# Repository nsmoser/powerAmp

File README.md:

Audio amplifier project implementing the LM3886 audio power amplifier.
Originally intended to replace a busted board in a powered subwoofer, but designed to be reused as a L/R stereo amp.
NOTE: the mute circuit was incorrectly connected to ground instead of the negative rail. Current draw necessary to unmute cannot be achieved unless the switch is connected to the negative rail.
Realistically, not all three matching pairs of caps in the cap bank are necessary. Connect the mute switch to one of the negative rail through holes in the cap bank if the bank isn't fully populated.
The low voltage power components are also not necessary for function. They are there to power peripherals (indicator lights, add-on pre-filters or pre-amps, etc.)

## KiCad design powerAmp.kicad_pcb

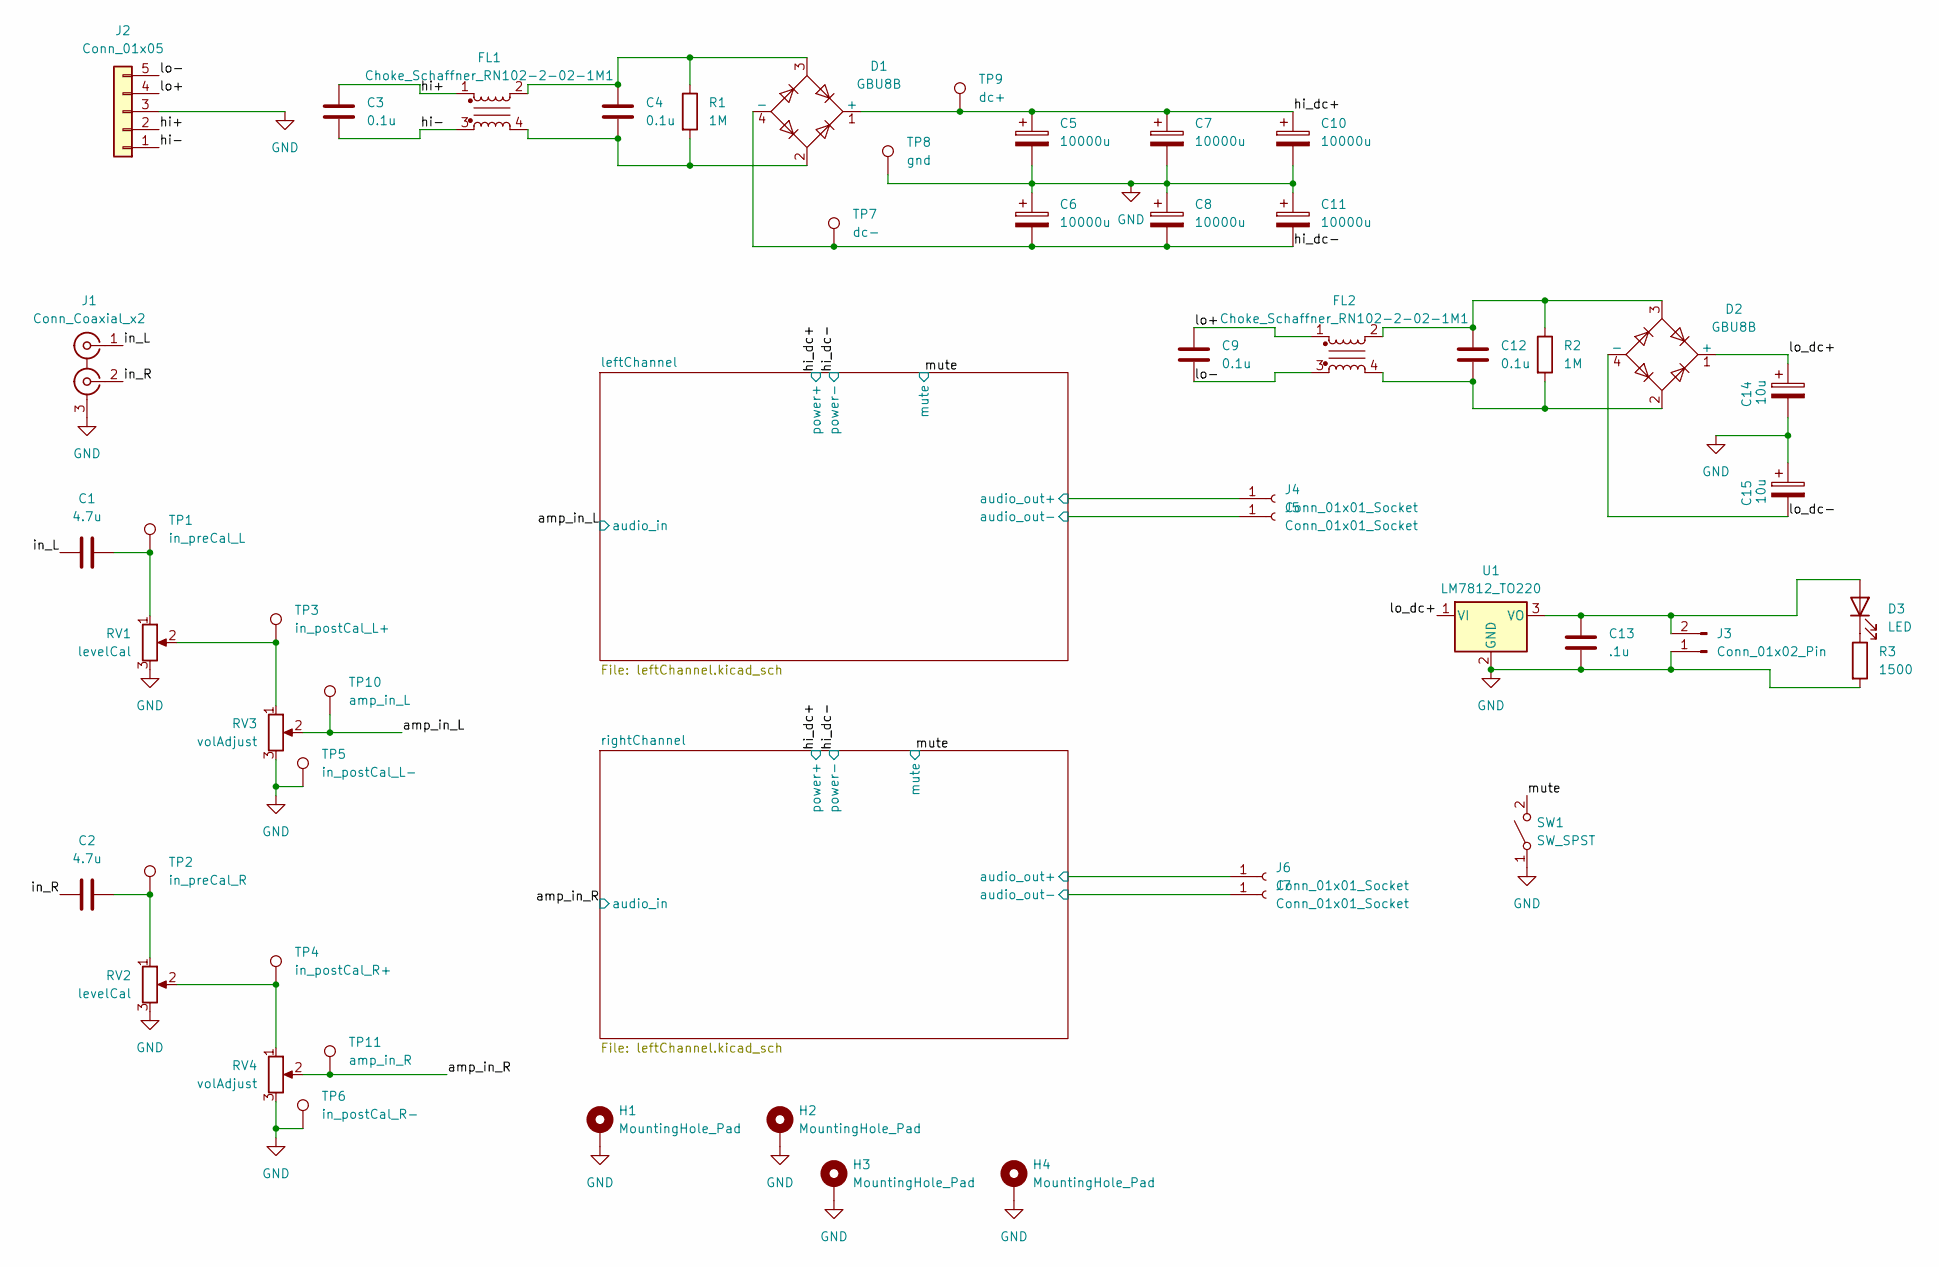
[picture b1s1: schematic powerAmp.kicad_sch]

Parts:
C1, C2: 4.7u; C_0805_2012Metric
C3, C4, C9, C12: 0.1u; C_1206_3216Metric
C5, C6, C7, C8, C10, C11: 10000u; CP_Radial_D35.0mm_P10.00mm_SnapIn
C13: .1u; C_0402_1005Metric
C14, C15: 10u; CP_Elec_5x5.3
D1, D2: GBU8B; Diode_Bridge_Vishay_GBU
D3: LED; PinSocket_1x02_P2.54mm_Vertical
FL1, FL2: Choke_Schaffner_RN102-2-02-1M1; Choke_Schaffner_RN102-04-14.0x14.0mm
H1, H2, H3, H4: MountingHole_Pad; MountingHole_4.3mm_M4_Pad_TopBottom
J1: Conn_Coaxial_x2; PinSocket_1x03_P2.54mm_Vertical
J2: Conn_01x05; PinSocket_1x05_P2.54mm_Vertical
J3: Conn_01x02_Pin; PinSocket_1x02_P2.54mm_Vertical
J4, J5, J6, J7: Conn_01x01_Socket; PinSocket_1x01_P2.54mm_Vertical
R1, R2: 1M; R_2512_6332Metric
R3: 1500; R_0603_1608Metric
RV1, RV2: levelCal; Potentiometer_Bourns_3009P_Horizontal
RV3, RV4: volAdjust; PinSocket_1x03_P2.54mm_Vertical
SW1: SW_SPST; PinSocket_1x02_P2.54mm_Vertical
TP1: in_preCal_L; TestPoint_Pad_1.0x1.0mm
TP2: in_preCal_R; TestPoint_Pad_1.0x1.0mm
TP3: in_postCal_L+; PinHeader_1x01_P2.54mm_Vertical
TP4: in_postCal_R+; PinHeader_1x01_P2.54mm_Vertical
TP5: in_postCal_L-; PinHeader_1x01_P2.54mm_Vertical
TP6: in_postCal_R-; PinHeader_1x01_P2.54mm_Vertical
TP7: dc-; TestPoint_Pad_1.0x1.0mm
TP8: gnd; TestPoint_Pad_1.0x1.0mm
TP9: dc+; TestPoint_Pad_1.0x1.0mm
TP10: amp_in_L; PinHeader_1x01_P2.54mm_Vertical
TP11: amp_in_R; PinHeader_1x01_P2.54mm_Vertical
U1: LM7812_TO220; TO-220-3_Vertical

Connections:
/amp_in_L: RV3.2, TP10.1; also elsewhere on the board
/amp_in_R: RV4.2, TP11.1; also elsewhere on the board
/hi+: C3.1, FL1.1, J2.2
/hi-: C3.2, FL1.3, J2.1
/hi_dc+: C5.1, C7.1, C10.1, D1.1 (+), TP9.1; also elsewhere on the board
/hi_dc-: C6.2, C8.2, C11.2, D1.4 (-), TP7.1; also elsewhere on the board
/in_L: C1.1, J1.1 (IN1)
/in_R: C2.1, J1.2 (IN2)
/leftChannel/audio_out+: J4.1; also elsewhere on the board
/leftChannel/audio_out-: J5.1; also elsewhere on the board
/lo+: C9.1, FL2.1, J2.4
/lo-: C9.2, FL2.3, J2.5
/lo_dc+: C14.1, D2.1 (+), U1.1 (VI)
/lo_dc-: C15.2, D2.4 (-)
/mute: SW1.2 (B); also elsewhere on the board
/rightChannel/audio_out+: J6.1; also elsewhere on the board
/rightChannel/audio_out-: J7.1; also elsewhere on the board
GND: C5.2, C6.1, C7.2, C8.1, C10.2, C11.1, C13.1, C14.2, C15.1, H1.1, H2.1, H3.1, H4.1, J1.3 (EXT), J2.3, J3.1, R3.2, RV1.3, RV2.3, RV3.3, RV4.3, SW1.1 (A), TP5.1, TP6.1, TP8.1, U1.2 (GND); also elsewhere on the board
unnamed: C1.2, RV1.1, TP1.1
unnamed: C2.2, RV2.1, TP2.1
unnamed: C4.1, D1.3, FL1.2, R1.1
unnamed: C4.2, D1.2, FL1.4, R1.2
unnamed: C12.1, D2.3, FL2.2, R2.1
unnamed: C12.2, D2.2, FL2.4, R2.2
unnamed: C13.2, D3.2 (A), J3.2, U1.3 (VO)
unnamed: D3.1 (K), R3.1
unnamed: RV1.2, RV3.1, TP3.1
unnamed: RV2.2, RV4.1, TP4.1

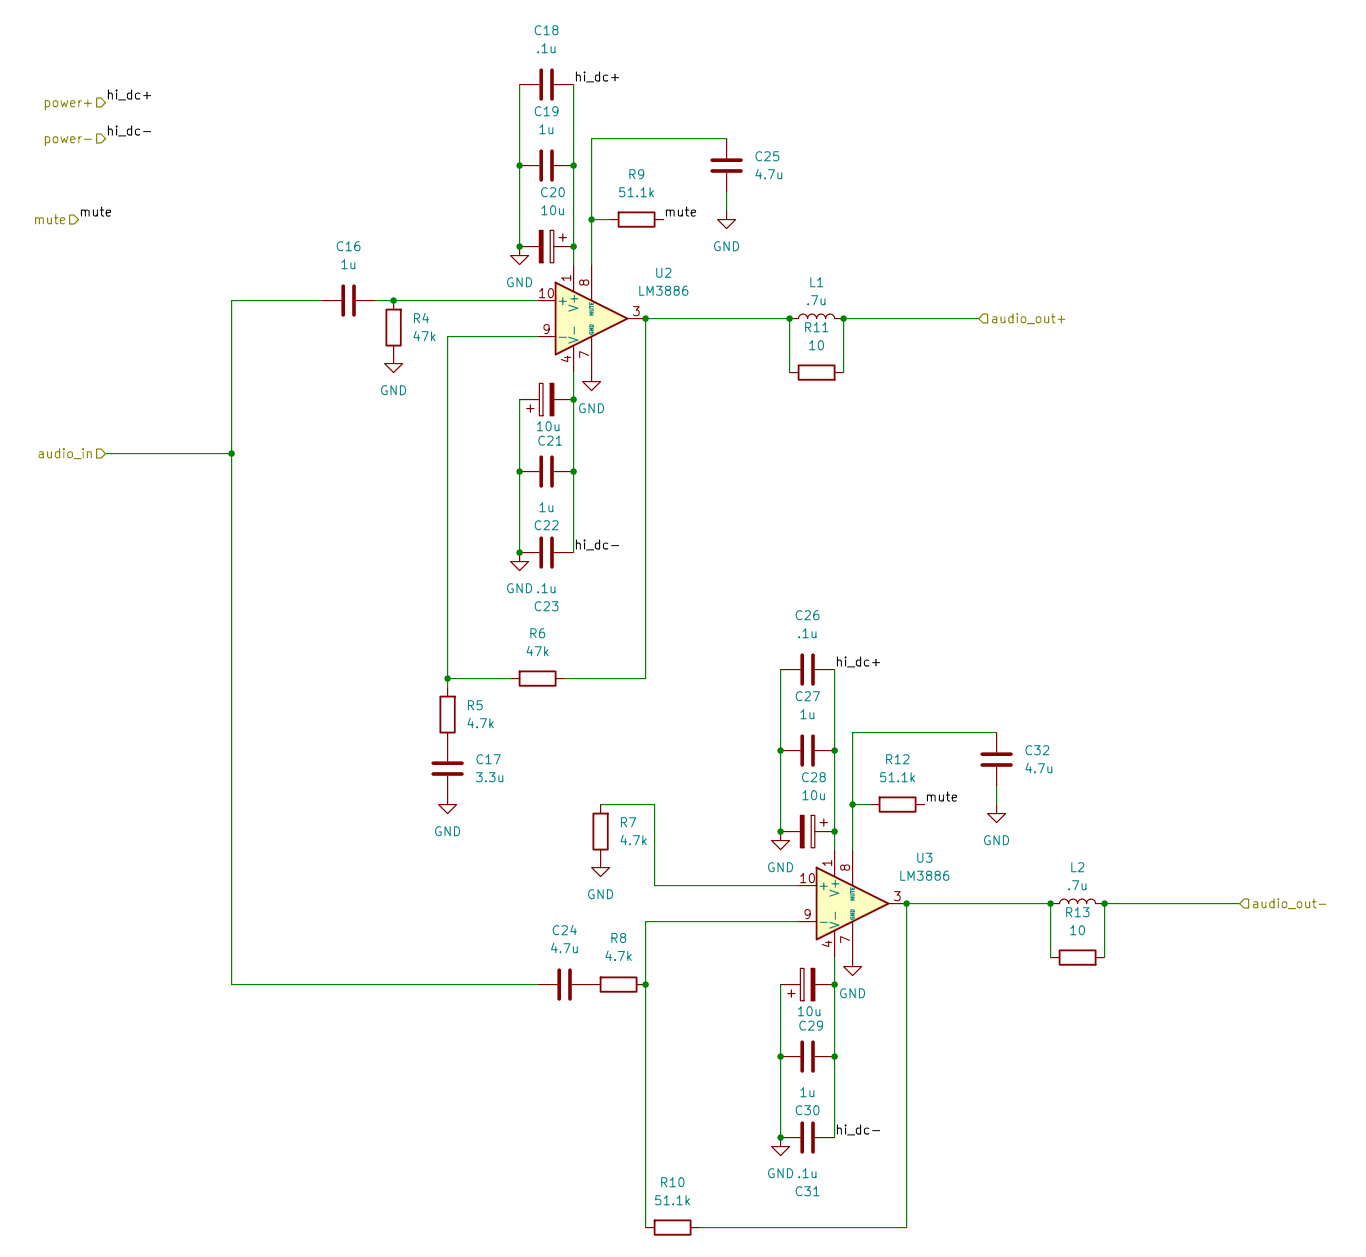
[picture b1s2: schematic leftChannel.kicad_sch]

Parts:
C16, C19, C22, C27, C30: 1u; C_0805_2012Metric
C17: 3.3u; C_1210_3225Metric
C18, C23, C26, C31: .1u; C_0402_1005Metric
C20, C21, C28, C29: 10u; CP_Elec_5x5.3
C24, C25, C32: 4.7u; C_0805_2012Metric
L1, L2: .7u; L_Vishay_IHLP-1616
R4, R6: 47k; R_0603_1608Metric
R5, R7, R8: 4.7k; R_0603_1608Metric
R9, R10, R12: 51.1k; R_0603_1608Metric
R11, R13: 10; PinSocket_1x02_P2.54mm_Vertical
U2, U3: LM3886; TO-220F-11_P3.4x5.08mm_StaggerOdd_Lead5.08mm_Vertical

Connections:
/amp_in_L: C16.1, C24.1; also elsewhere on the board
/hi_dc+: C18.2, C19.2, C20.1, C26.2, C27.2, C28.1, U2.1 (V+), U2.5 (V+), U3.1 (V+), U3.5 (V+); also elsewhere on the board
/hi_dc-: C21.2, C22.1, C23.1, C29.2, C30.1, C31.1, U2.4 (V-), U3.4 (V-); also elsewhere on the board
/leftChannel/audio_out+: L1.2, R11.2; also elsewhere on the board
/leftChannel/audio_out-: L2.2, R13.2; also elsewhere on the board
/mute: R9.1, R12.1; also elsewhere on the board
GND: C17.1, C18.1, C19.1, C20.2, C21.1, C22.2, C23.2, C25.1, C26.1, C27.1, C28.2, C29.1, C30.2, C31.2, C32.1, R4.1, R7.1, U2.7 (GND), U3.7 (GND); also elsewhere on the board
unnamed: C17.2, R5.1
unnamed: C24.2, R8.2
unnamed: L1.1, R6.1, R11.1, U2.3
unnamed: L2.1, R10.1, R13.1, U3.3
unnamed: C16.2, R4.2, U2.10 (+)
unnamed: R5.2, R6.2, U2.9 (-)
unnamed: C25.2, R9.2, U2.8 (MUTE)
unnamed: R7.2, U3.10 (+)
unnamed: R8.1, R10.2, U3.9 (-)
unnamed: C32.2, R12.2, U3.8 (MUTE)

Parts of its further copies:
C33, C36, C39, C44, C47: 1u; C_0805_2012Metric
C34: 3.3u; C_1210_3225Metric
C35, C40, C43, C48: .1u; C_0402_1005Metric
C37, C38, C45, C46: 10u; CP_Elec_5x5.3
C41, C42, C49: 4.7u; C_0805_2012Metric
L3, L4: .7u; L_Vishay_IHLP-1616
R14, R16: 47k; R_0603_1608Metric
R15, R17, R18: 4.7k; R_0603_1608Metric
R19, R20, R22: 51.1k; R_0603_1608Metric
R21, R23: 10; PinSocket_1x02_P2.54mm_Vertical
U4, U5: LM3886; TO-220F-11_P3.4x5.08mm_StaggerOdd_Lead5.08mm_Vertical

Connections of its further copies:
/amp_in_R: C33.1, C41.1; also elsewhere on the board
/hi_dc+: C35.2, C36.2, C37.1, C43.2, C44.2, C45.1, U4.1 (V+), U4.5 (V+), U5.1 (V+), U5.5 (V+); also elsewhere on the board
/hi_dc-: C38.2, C39.1, C40.1, C46.2, C47.1, C48.1, U4.4 (V-), U5.4 (V-); also elsewhere on the board
/mute: R19.1, R22.1; also elsewhere on the board
/rightChannel/audio_out+: L3.2, R21.2; also elsewhere on the board
/rightChannel/audio_out-: L4.2, R23.2; also elsewhere on the board
GND: C34.1, C35.1, C36.1, C37.2, C38.1, C39.2, C40.2, C42.1, C43.1, C44.1, C45.2, C46.1, C47.2, C48.2, C49.1, R14.1, R17.1, U4.7 (GND), U5.7 (GND); also elsewhere on the board
unnamed: C34.2, R15.1
unnamed: C41.2, R18.2
unnamed: L3.1, R16.1, R21.1, U4.3
unnamed: L4.1, R20.1, R23.1, U5.3
unnamed: C33.2, R14.2, U4.10 (+)
unnamed: R15.2, R16.2, U4.9 (-)
unnamed: C42.2, R19.2, U4.8 (MUTE)
unnamed: R17.2, U5.10 (+)
unnamed: R18.1, R20.2, U5.9 (-)
unnamed: C49.2, R22.2, U5.8 (MUTE)

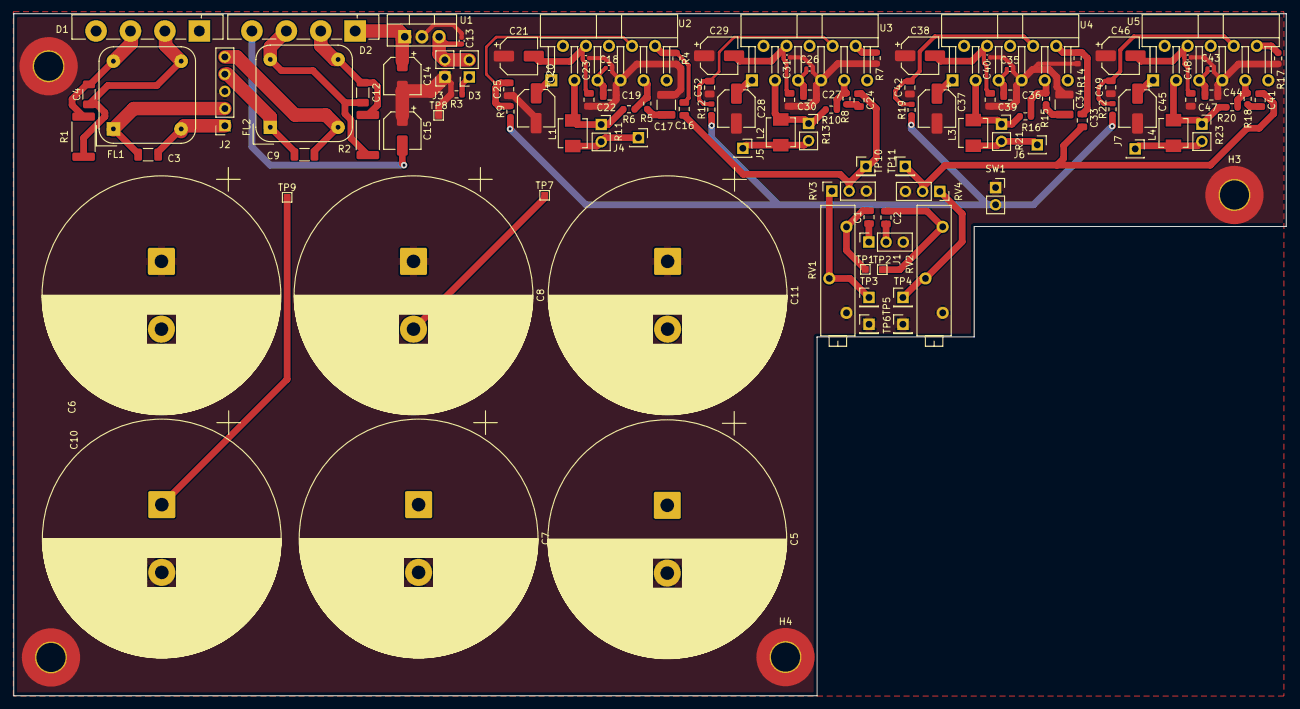
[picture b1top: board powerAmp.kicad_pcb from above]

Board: 6 copper layers, 187.8 x 100.6 mm, 113 parts (0 on the bottom side), 48 nets.

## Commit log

2026-06-12 Initial Upload
    Capture project to ensure visibility. Kicad project file, schematics, PCB, and BOM
